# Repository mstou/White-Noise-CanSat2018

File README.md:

# White Noise
[White Noise](https://www.facebook.com/WhiteNoiseGRE/) is a space-engineering team from the National Technical University of Athens and currently consists of 6 members ( in alphabetical order ) :

 - Dimitris Bralios
 - Chariton Charitonidis
 - Iasonas Nikolaou
 - Spyros Pavlatos
 - George Rapakoulias
 - Miltiadis Stouras

Our team won 1st prize in the [CanSat in Greece 2018](https://cansat.gr/) competition.

# DrillSat

This repository hosts the electrical circuits, mechanical drawings and software of our CanSat. Our goal was to develop a CanSat that can help in exploring new planets, as a part of our idea to use CubeSats in space exploration. Specifically, our CanSat, after a successful landing with the parachute, is able to use its [leg mechanism](https://www.youtube.com/watch?v=kTSUgSXn8OM) and rise into a position from which it can dig its drills to the ground and measure the soil's moisture with a sensor we developed.
You can find our ground station [here](https://github.com/MStou/CanSat2018-Ground-Station).

Our team, after facing many difficulties developing the prototype, decided to be fully open source and released all of our work to make sure that future teams will not have to "re-invent the wheel".

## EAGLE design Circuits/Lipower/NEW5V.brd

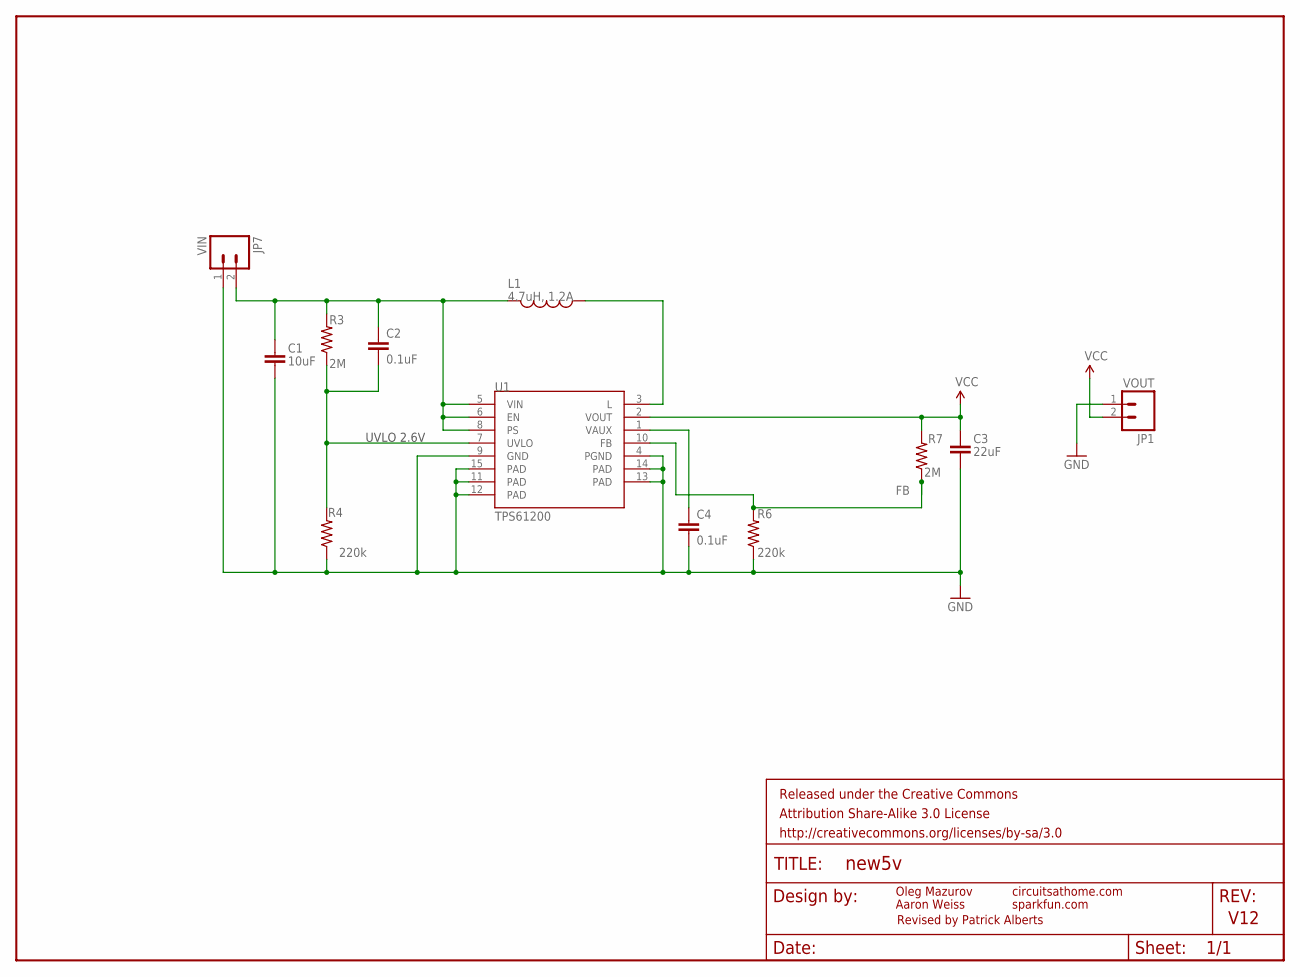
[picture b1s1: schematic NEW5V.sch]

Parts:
C1: 10uF; 1206
C2, C4: 0.1uF; 0603-CAP
C3: 22uF; 0805
FRAME1: FRAME-LETTER; CREATIVE_COMMONS
JP1: VOUT; 1X02
JP7: VIN; 1X02
L1: 4.7uH, 1.2A; CDRH2D09
R3, R7: 2M; 0603-RES
R4, R6: 220k; 0603-RES
U1: TPS61200; QFN-10_PAD

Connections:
FB: R6.2, R7.1, U1.10 (FB)
GND: C1.2, C3.2, C4.2, JP1.1, JP7.1, R4.1, R6.1, U1.4 (PGND), U1.9 (GND), U1.11 (PAD), U1.12 (PAD), U1.13 (PAD), U1.14 (PAD), U1.15 (PAD)
unnamed: C4.1, U1.1 (VAUX)
unnamed: L1.P$1 (1), U1.3 (L)
UVLO: C2.2, R3.1, R4.2, U1.7 (UVLO)
VCC: C3.1, JP1.2, R7.2, U1.2 (VOUT)
VIN: C1.1, C2.1, JP7.2, L1.P$2 (2), R3.2, U1.5 (VIN), U1.6 (EN), U1.8 (PS)

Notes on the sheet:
UVLO 2.6V
circuitsathome.com
Oleg Mazurov
Aaron Weiss
sparkfun.com
V12
Revised by Patrick Alberts

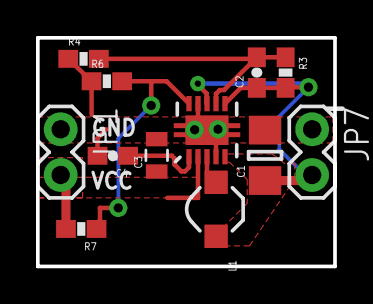
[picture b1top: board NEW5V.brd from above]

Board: 2 copper layers, 16.5 x 12.7 mm, 13 parts (0 on the bottom side), 7 nets.

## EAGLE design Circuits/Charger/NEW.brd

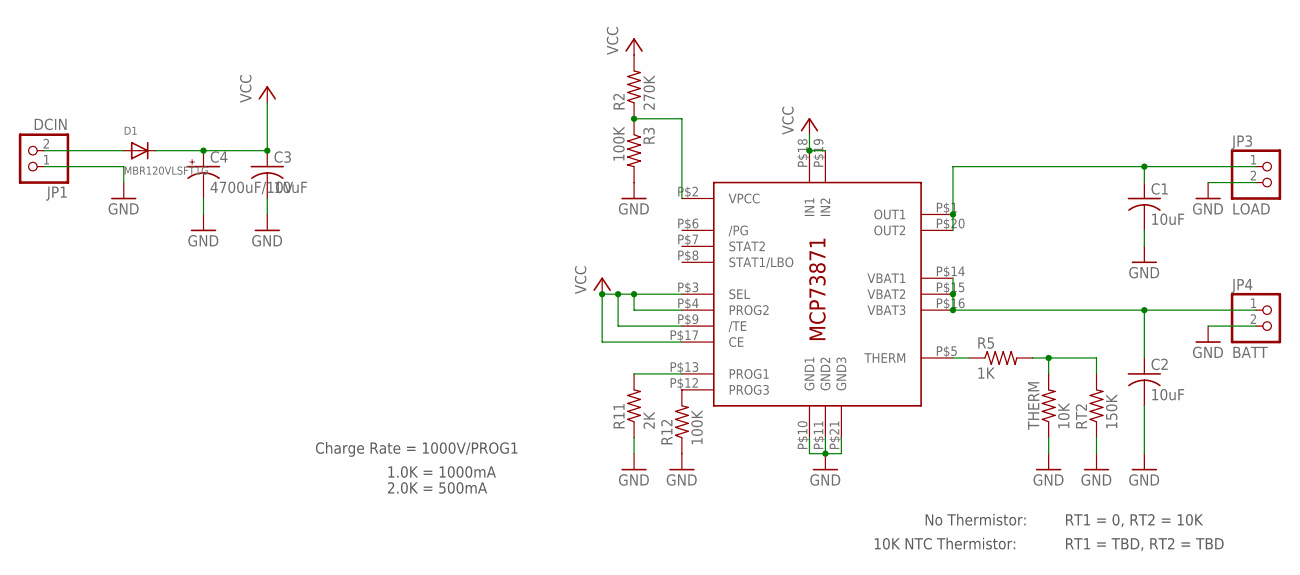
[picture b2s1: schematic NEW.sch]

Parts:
C1, C2, C3: 10uF; C0805K
C4: 4700uF/10V; E5-10,5
D1: MBR120VLSFT1G; SOD-123
IC1: MCP73871; QFN20_4MM
JP1: DCIN; 1X02_OVAL
JP3: LOAD; 1X02_ROUND
JP4: BATT; 1X02_ROUND
R2: 270K; R0805
R3, R12: 100K; R0805
R5: 1K; M0805
R11: 2K; M0805
RT2: 150K; M0805
THERM: 10K; M0805

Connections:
BATT: C2.1, IC1.P$14 (VBAT1), IC1.P$15 (VBAT2), IC1.P$16 (VBAT3), JP4.1
GND: C1.2, C2.2, C3.2, C4.-, IC1.P$10 (GND1), IC1.P$11 (GND2), IC1.P$21 (GND3), JP1.1, JP3.2, JP4.2, R3.2, R11.1, R12.1, RT2.1, THERM.1
unnamed: D1.A, JP1.2
unnamed: IC1.P$5 (THERM), R5.1
unnamed: IC1.P$2 (VPCC), R2.1, R3.1
unnamed: R5.2, RT2.2, THERM.2
unnamed: IC1.P$12 (PROG3), R12.2
unnamed: IC1.P$13 (PROG1), R11.2
OUT: C1.1, IC1.P$1 (OUT1), IC1.P$20 (OUT2), JP3.1
VCC: C3.1, C4.+, D1.C, IC1.P$3 (SEL), IC1.P$4 (PROG2), IC1.P$9 (/TE), IC1.P$17 (CE), IC1.P$18 (IN1), IC1.P$19 (IN2), R2.2

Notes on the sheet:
Charge Rate = 1000V/PROG1
1.0K = 1000mA
2.0K = 500mA
No Thermistor:
10K NTC Thermistor:
RT1 = 0, RT2 = 10K
RT1 = TBD, RT2 = TBD

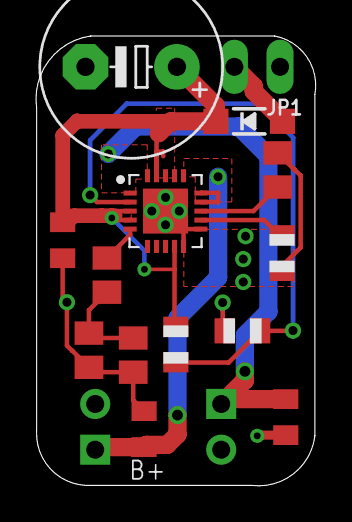
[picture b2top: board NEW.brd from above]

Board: 2 copper layers, 15.5 x 25.0 mm, 16 parts (0 on the bottom side), 10 nets.

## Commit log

2018-04-13 Added License
2018-04-13 Added README
2018-04-13 Added Arduino's code and configuration files from xbee and gps
2018-04-13 Added the Mechanical Drawings made by George Rapakoulias
2018-04-13 Added the Pre-Launch Report of our CanSat
2018-04-13 Added the circuit designs by Dimitris Bralios
2018-10-07 Add Cansat Final Paper 2018

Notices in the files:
parts and their libraries:
SparkFun-Aesthetics: Licensing: CC v3.0 Share-Alike You are welcome to use this library for commercial purposes.
SparkFun-Aesthetics: Released under the Creative Commons Attribution Share-Alike 3.0 License
SparkFun-Aesthetics: http://creativecommons.org/licenses/by-sa/3.0
